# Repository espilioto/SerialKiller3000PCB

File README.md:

# SerialKiller3000PCB
Very PCB. Much eagle. Wow.

I know having all the revisions saved is overkill, but it's nice seeing my progress (I didn't start using git with eagle till much later).
You can also see the point where I deemed this project worthy enough to send to a PCB [manufacturing company].
(Also, yes, autorouter for the most part. Don't hate me!)

The board turned out really nice, even though I will enlarge the logo on the back a bit, 
add another decoupling cap next to the 12 volt input header and make some other minor changes in the next version.

Renders made with [EagleUp].

[Main project]

***SouLSLayeR***

[manufacturing company]:http://www.eurocircuits.com/
[Main project]:https://github.com/espilioto/SerialKiller3000
[EagleUp]:https://eagleup.wordpress.com/

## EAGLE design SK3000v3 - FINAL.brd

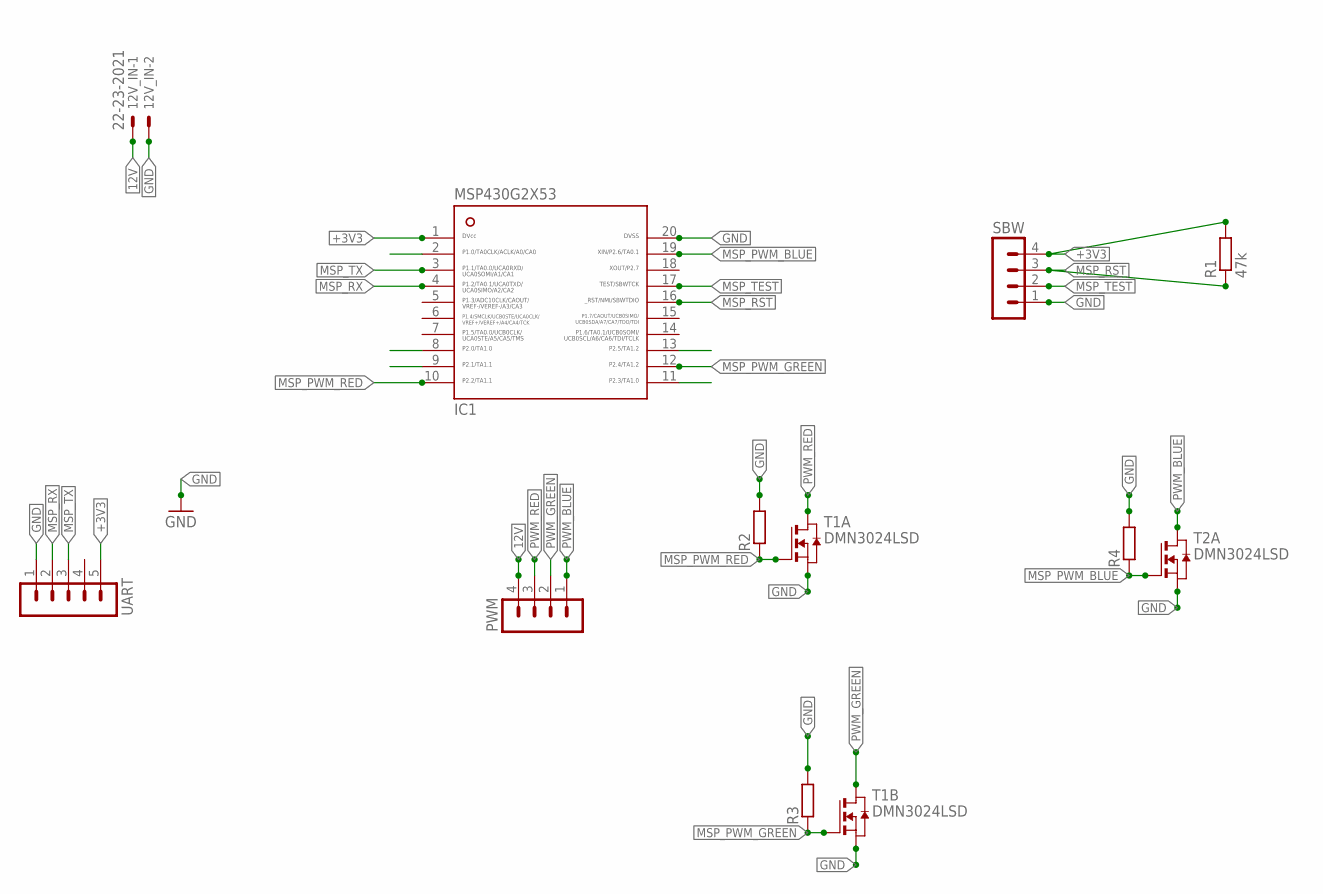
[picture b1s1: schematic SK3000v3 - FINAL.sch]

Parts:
12V_IN: 22-23-2021
IC1: MSP430G2553; PW20
PWM: MA04-1
R1: 47k; 0207/5V
R2, R3, R4: R-EU_0207/5V; 0207/5V
SBW: MA04-1
T1, T2: DMN3024LSD; SO8
UART: MA05-1

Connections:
12V: 12V_IN.1, PWM.4
+3V3: IC1.1, R1.2, SBW.4, UART.5
GND: 12V_IN.2, IC1.20, R2.2, R3.2, R4.2, SBW.1, T1.1 (S), T1.3 (S), T2.1 (S), UART.1
MSP_PWM_BLUE: IC1.19, R4.1, T2.2 (G)
MSP_PWM_GREEN: IC1.12, R3.1, T1.4 (G)
MSP_PWM_RED: IC1.10, R2.1, T1.2 (G)
MSP_RST: IC1.16, R1.1, SBW.3
MSP_RX: IC1.4, UART.2
MSP_TEST: IC1.17, SBW.2
MSP_TX: IC1.3, UART.3
PWM_BLUE: PWM.1, T2.7 (D), T2.8 (D)
PWM_GREEN: PWM.2, T1.5 (D), T1.6 (D)
PWM_RED: PWM.3, T1.7 (D), T1.8 (D)

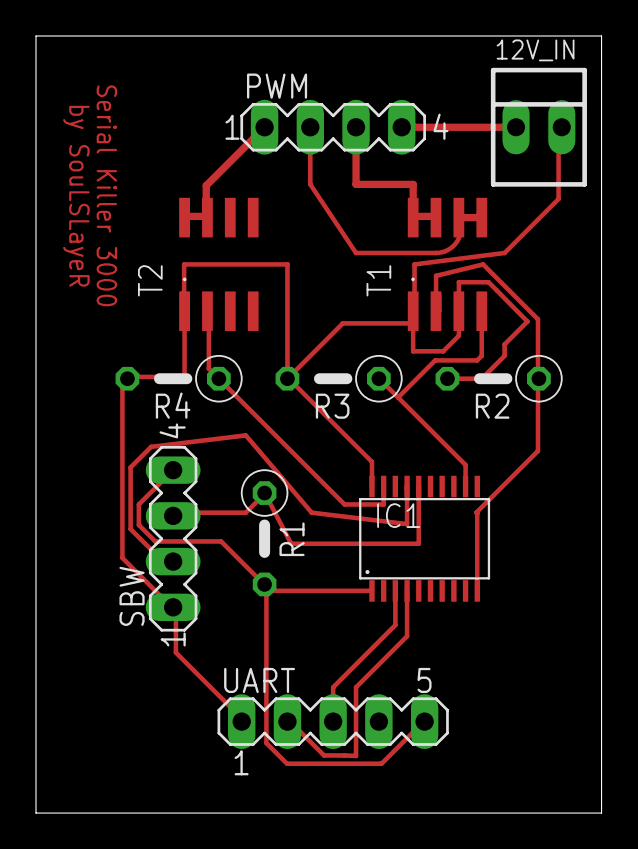
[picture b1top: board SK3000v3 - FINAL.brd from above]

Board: 2 copper layers, 31.4 x 43.2 mm, 11 parts (0 on the bottom side), 13 nets.

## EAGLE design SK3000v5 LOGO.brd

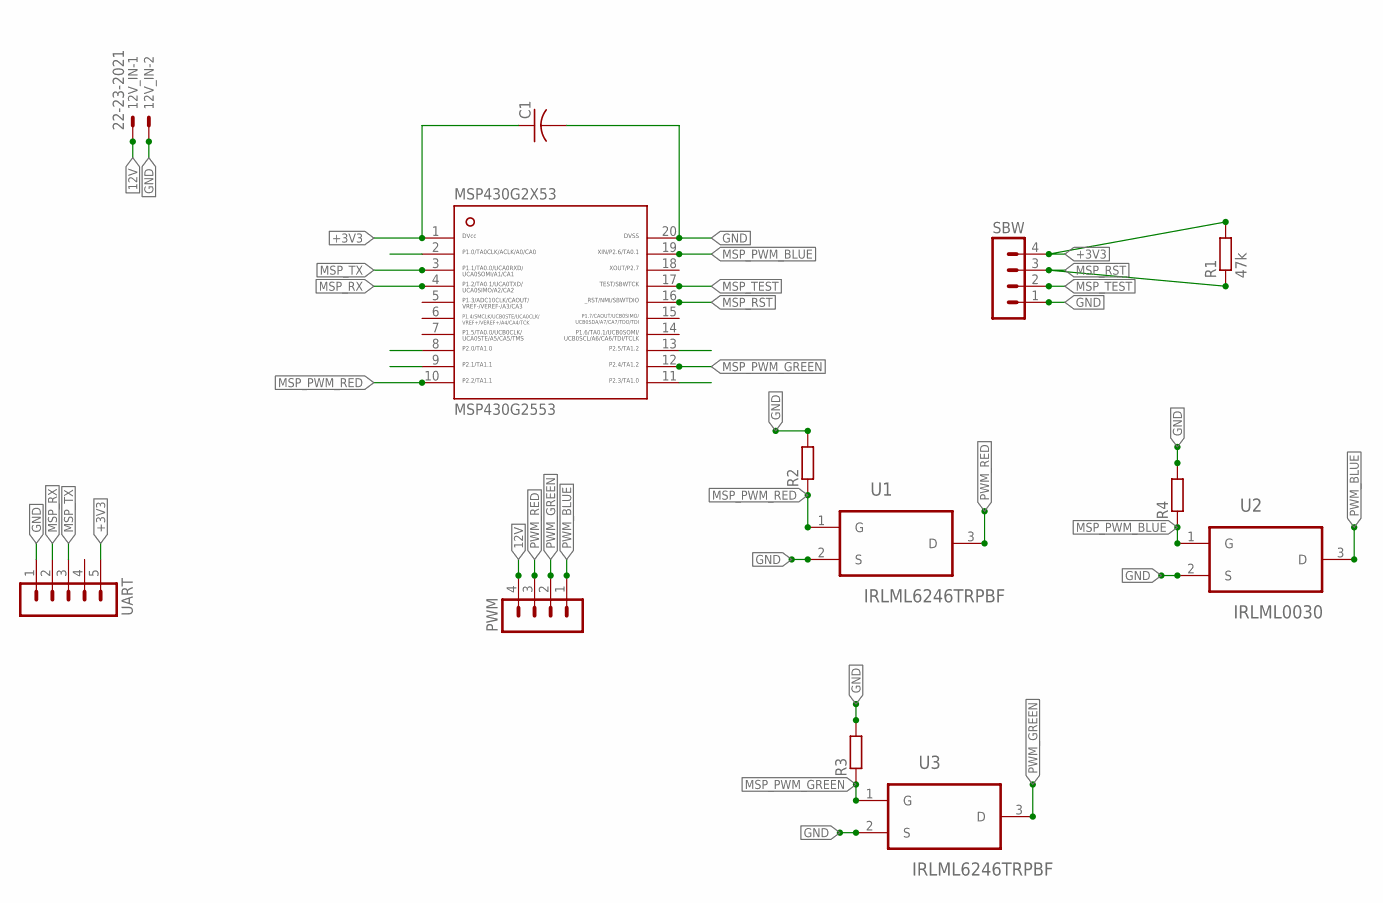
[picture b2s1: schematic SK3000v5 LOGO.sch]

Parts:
12V_IN: 22-23-2021
C1: C-USC0603; C0603
MSP430G2553: MSP430G2X53-20PW20; PW20
PWM: MA04-1
R1: 47k; R0603
R2, R3, R4: R-EU_R0603; R0603
SBW: MA04-1
U1, U3: IRLML6246TRPBF; SOT95P240X112-3N
U2: IRLML0030; SOT95P240X112-3N
UART: MA05-1

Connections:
12V: 12V_IN.1, PWM.4
+3V3: C1.1, MSP430G2553.1, R1.2, SBW.4, UART.5
GND: 12V_IN.2, C1.2, MSP430G2553.20, R2.2, R3.2, R4.2, SBW.1, U1.2 (S), U2.2 (S), U3.2 (S), UART.1
MSP_PWM_BLUE: MSP430G2553.19, R4.1, U2.1 (G)
MSP_PWM_GREEN: MSP430G2553.12, R3.1, U3.1 (G)
MSP_PWM_RED: MSP430G2553.10, R2.1, U1.1 (G)
MSP_RST: MSP430G2553.16, R1.1, SBW.3
MSP_RX: MSP430G2553.4, UART.2
MSP_TEST: MSP430G2553.17, SBW.2
MSP_TX: MSP430G2553.3, UART.3
PWM_BLUE: PWM.1, U2.3 (D)
PWM_GREEN: PWM.2, U3.3 (D)
PWM_RED: PWM.3, U1.3 (D)

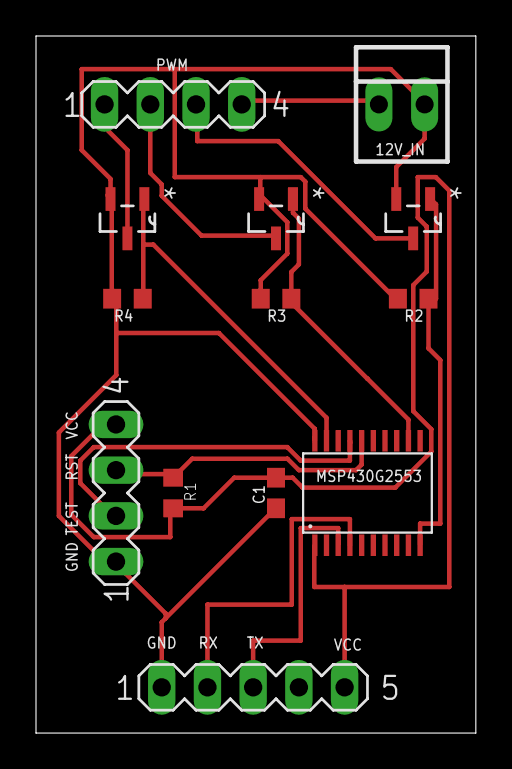
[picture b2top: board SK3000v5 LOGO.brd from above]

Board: 2 copper layers, 24.4 x 38.7 mm, 13 parts (0 on the bottom side), 13 nets.
